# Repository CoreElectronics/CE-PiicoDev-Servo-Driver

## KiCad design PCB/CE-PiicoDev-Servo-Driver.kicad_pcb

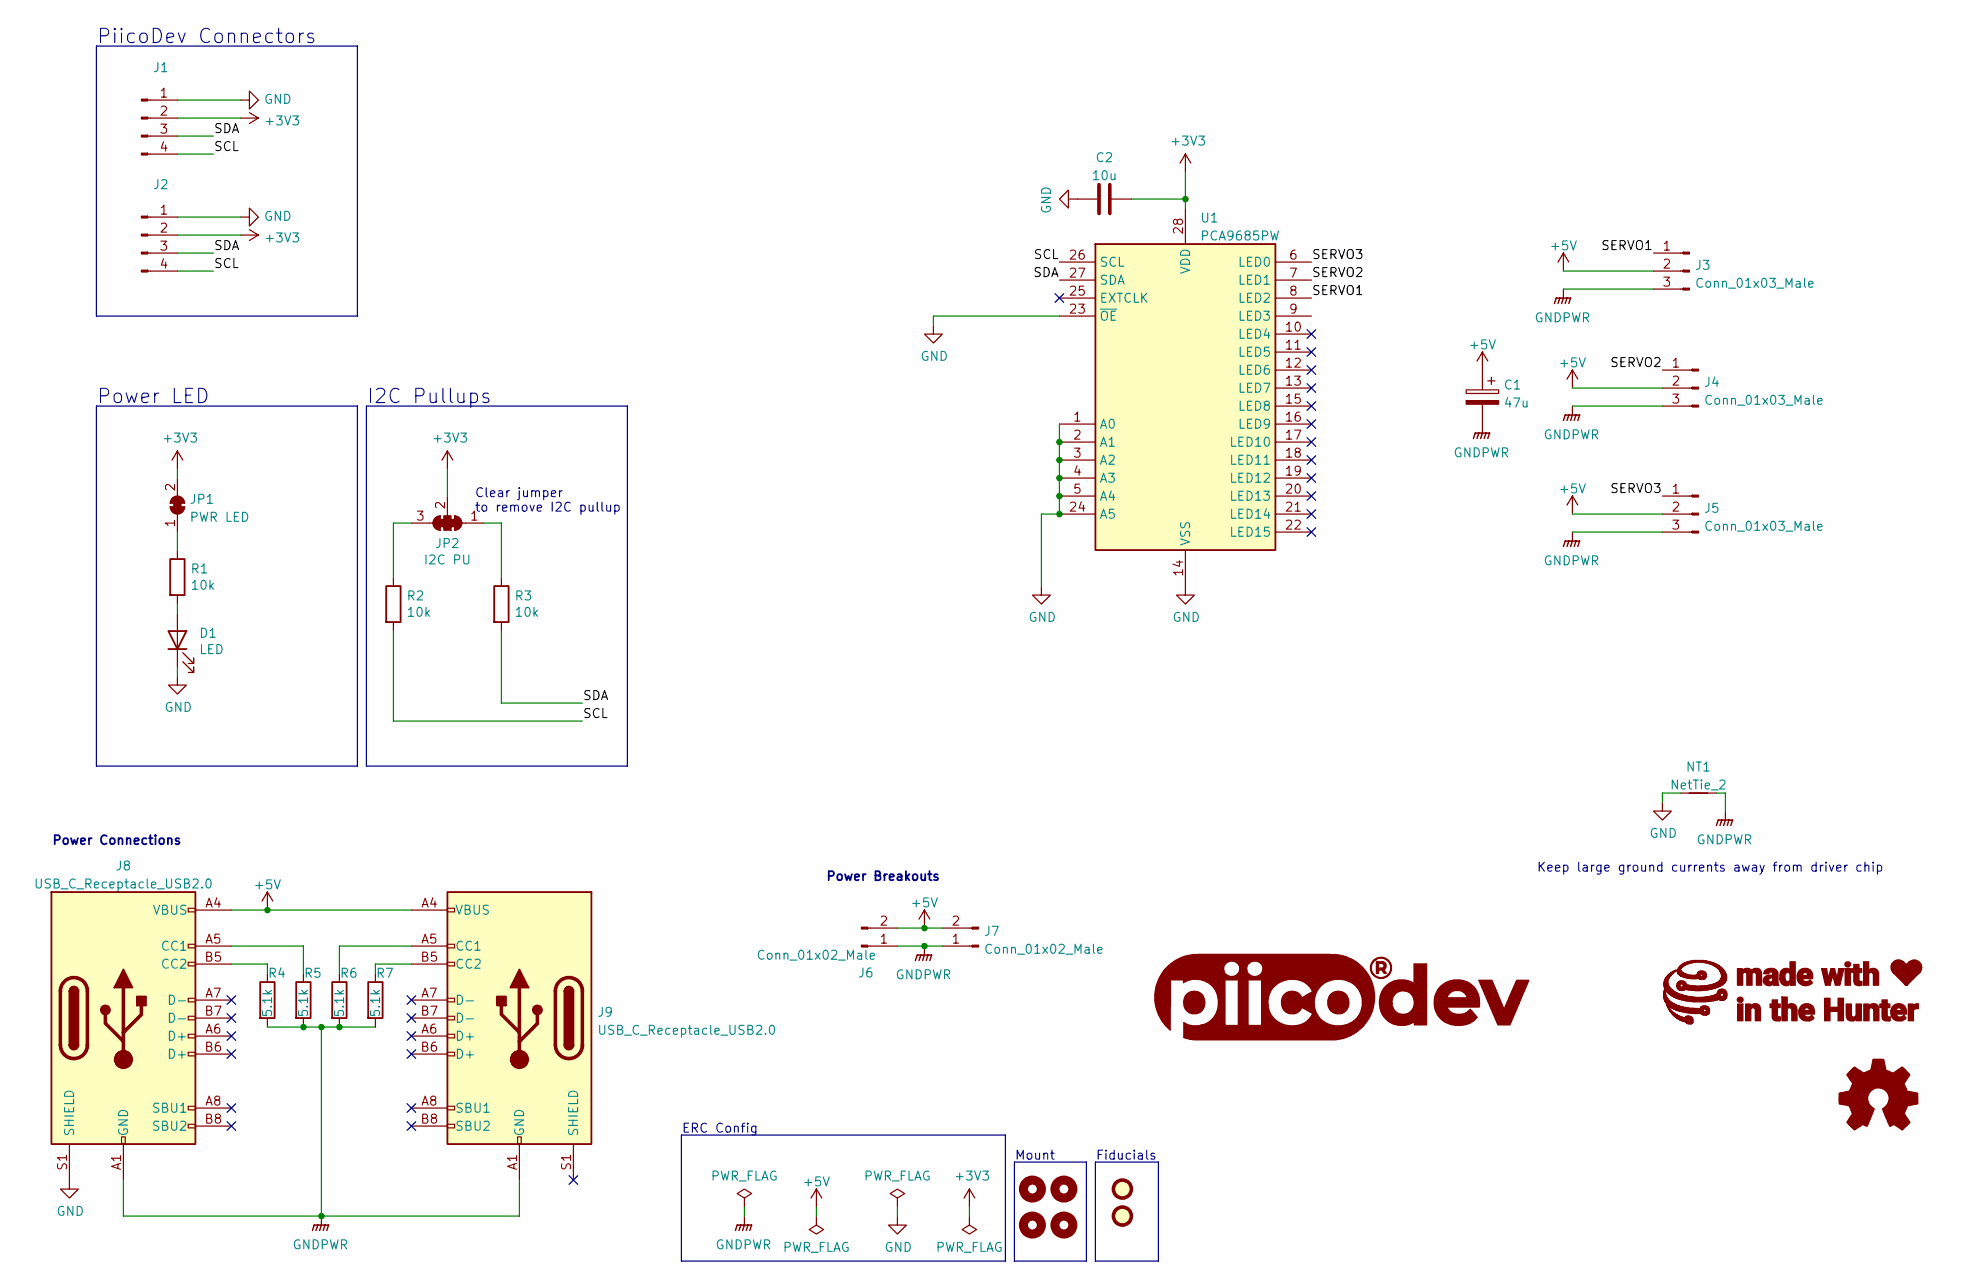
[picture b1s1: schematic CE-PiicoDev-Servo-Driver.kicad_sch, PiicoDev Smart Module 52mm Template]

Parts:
C1: 47u; CP_Elec_6.3x5.3
C2: 10u; C_0603_1608Metric
D1: LED; LED_0603_1608Metric
FID1, FID2: Fiducial; Fiducial_1mm_Mask2mm
G1: LOGO_PiicoDev; piicodev_logo_14.2x3.4mm
G2: LOGO_CoreElectronics_no-text; CoreElectronics_logo_5mm_v2
G3: LOGO_made-with-love; piicodev_logo_14.2x3.4mm
H1, H2, H3, H4: MountingHole; MountingHole_2.7mm_M2.5_PadClearance_1.2
J1, J2: JST_SH_SM04B-SRSS-TB_1x04-1MP_P1.00mm_Horizontal
J3, J4, J5: Conn_01x03_Male; PinHeader_1x03_P2.54mm_Vertical_SMD_Symmetric
J6, J7: Conn_01x02_Male; PinHeader_1x02_P2.54mm_Vertical
J8, J9: USB_C_Receptacle_USB2.0; USB_C_Receptacle_HRO_TYPE-C-31-M-12
JP1: PWR LED; SolderJumper-2_P1.3mm_Bridged_RoundedPad1.0x1.5mm
JP2: I2C PU; SolderJumper-3_P1.3mm_Closed_RoundedPad1.0x1.5mm_NumberLabe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
LOGO1: Logo_Open_Hardware_Small; oshw
NT1: NetTie_2; NetTie-2_SMD_Pad2.0mm
R1, R2, R3: 10k; R_0402_1005Metric
R4, R5, R6, R7: 5.1k; R_0402_1005Metric
U1: PCA9685PW; TSSOP-28_4.4x9.7mm_P0.65mm

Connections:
+3V3: C2.1, J1.2, J2.2, JP1.2 (B), JP2.2 (C), U1.28 (VDD)
+5V: C1.1, J3.2, J4.2, J5.2, J6.2, J7.2, J8.A4 (VBUS), J8.A9 (VBUS), J8.B4 (VBUS), J8.B9 (VBUS), J9.A4 (VBUS), J9.A9 (VBUS), J9.B4 (VBUS), J9.B9 (VBUS)
/SCL: J1.4, J2.4, R2.2, U1.26 (SCL)
/SDA: J1.3, J2.3, R3.2, U1.27 (SDA)
/SERVO1: J3.1, U1.8 (LED2)
/SERVO2: J4.1, U1.7 (LED1)
/SERVO3: J5.1, U1.6 (LED0)
GND: C2.2, D1.1 (K), J1.1, J2.1, J8.S1 (SHIELD), NT1.1, U1.1 (A0), U1.2 (A1), U1.3 (A2), U1.4 (A3), U1.5 (A4), U1.14 (VSS), U1.23 (~OE), U1.24 (A5)
GNDPWR: C1.2, J3.3, J4.3, J5.3, J6.1, J7.1, J8.A1 (GND), J8.A12 (GND), J8.B1 (GND), J8.B12 (GND), J9.A1 (GND), J9.A12 (GND), J9.B1 (GND), J9.B12 (GND), NT1.2, R4.2, R5.2, R6.2, R7.2
unnamed: D1.2 (A), R1.2
unnamed: J8.A5 (CC1), R5.1
unnamed: J8.B5 (CC2), R4.1
unnamed: J9.A5 (CC1), R6.1
unnamed: J9.B5 (CC2), R7.1
unnamed: JP2.1 (A), R3.1
unnamed: JP2.3 (B), R2.1
unnamed: JP1.1 (A), R1.1

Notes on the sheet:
PiicoDev Connectors
I2C Pullups
Keep large ground currents away from driver chip
Power LED
Power Connections
Mount
Clear jumper to remove I2C pullup
Power Breakouts
ERC Config
Fiducials

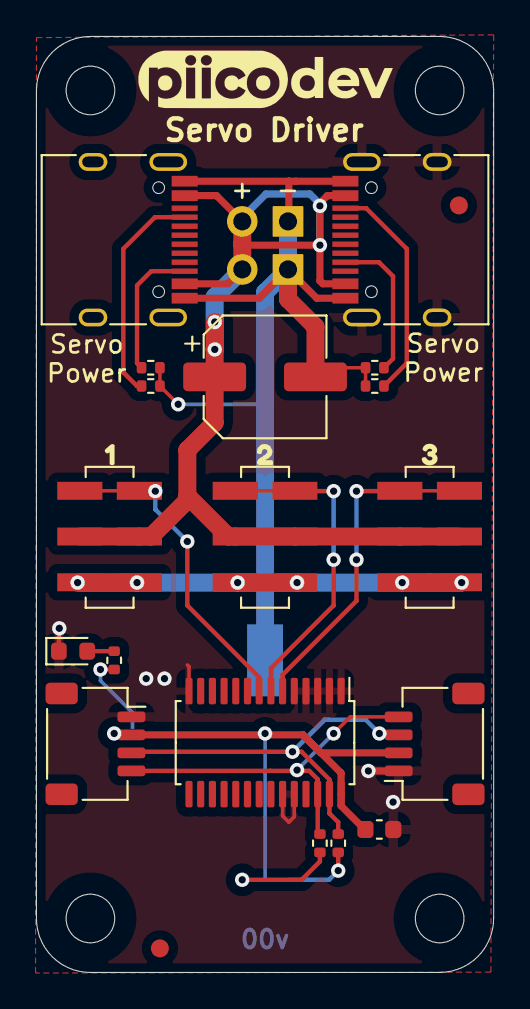
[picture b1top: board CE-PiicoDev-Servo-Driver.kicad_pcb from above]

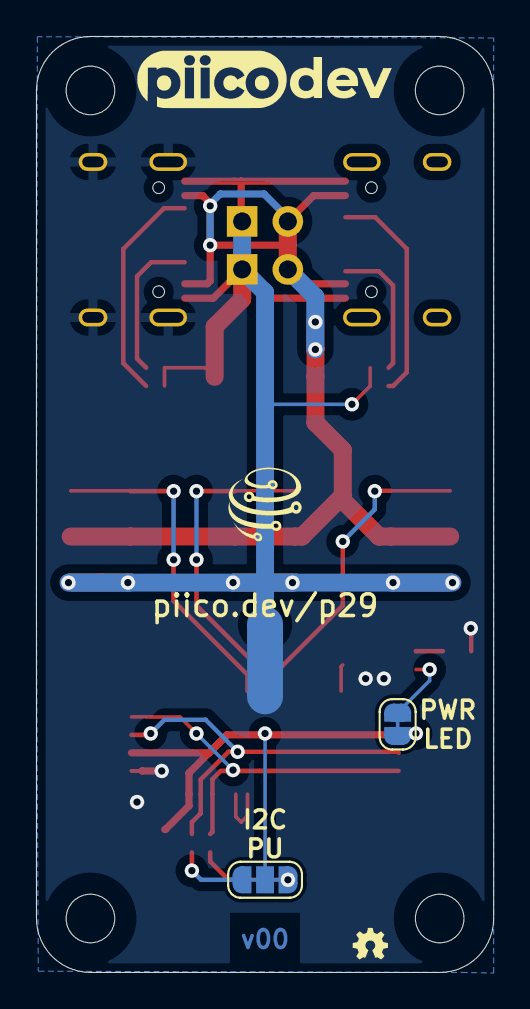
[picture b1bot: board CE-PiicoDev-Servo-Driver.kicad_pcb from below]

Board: 2 copper layers, 25.4 x 52.0 mm, 36 parts (6 on the bottom side), 17 nets.

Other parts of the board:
kibuzzard-6360811E: G***; kibuzzard-6360811E
kibuzzard-6360812A: G***; kibuzzard-6360812A
kibuzzard-63608105: G***; kibuzzard-63608105

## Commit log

2022-11-01 initial commit v00
2022-12-02 include paste on USB connector support tabs

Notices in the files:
PCB/CE-PiicoDev-Servo-Driver.kicad_sch:
License: CCASAv4.0 http://creativecommons.org/licenses/by-sa/4.0
